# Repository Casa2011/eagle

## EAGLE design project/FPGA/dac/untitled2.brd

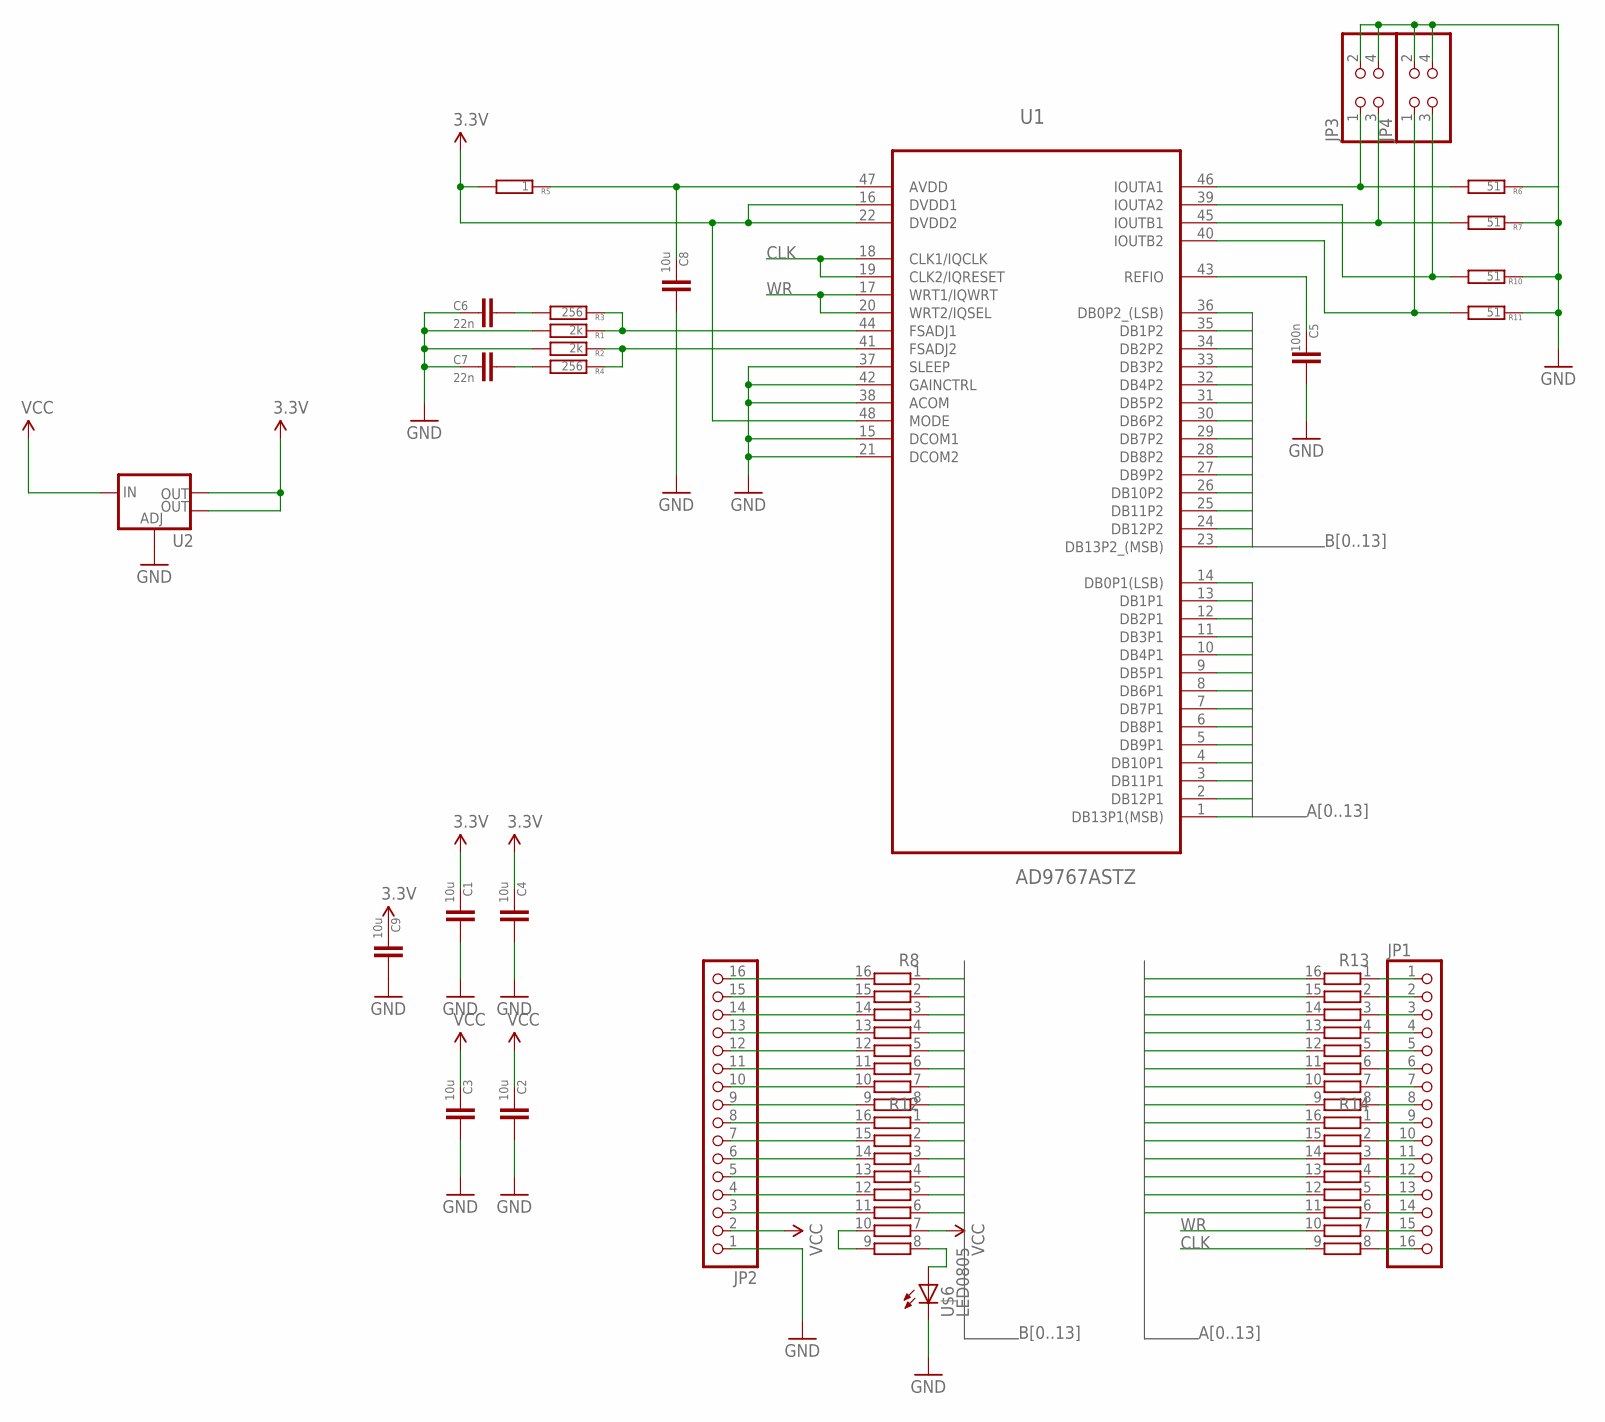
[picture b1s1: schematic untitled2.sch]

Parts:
C1, C2, C3, C4, C8, C9: 10u; C0805
C5: 100n; C0805
C6, C7: 22n; C0805
JP1, JP2: PINHD-1X16_2.54; 1X16
JP3, JP4: PINHD-2X02_2.54-SMD; 2X02SMD
R1, R2: 2k; R0805
R3, R4: 256; R0805
R5: 1; 0603
R6, R7, R10, R11: 51; R0805
R8, R12, R13, R14: 4816P-T01; 4816P
U1: AD9767ASTZ; QFP50P900X900X160-48N
U2: V_REG_LM1117SOT223; SOT223
U$6: LED0805; 0805-LED

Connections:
3.3V: C1.2, C4.2, C9.2, R5.2, U1.16 (DVDD1), U1.22 (DVDD2), U1.48 (MODE), U2.2 (OUT), U2.4 (OUT)
A0: R14.11, U1.14 (DB0P1(LSB))
A1: R14.12, U1.13 (DB1P1)
A2: R14.13, U1.12 (DB2P1)
A3: R14.14, U1.11 (DB3P1)
A4: R14.15, U1.10 (DB4P1)
A5: R14.16, U1.9 (DB5P1)
A6: R13.9, U1.8 (DB6P1)
A7: R13.10, U1.7 (DB7P1)
A8: R13.11, U1.6 (DB8P1)
A9: R13.12, U1.5 (DB9P1)
A10: R13.13, U1.4 (DB10P1)
A11: R13.14, U1.3 (DB11P1)
A12: R13.15, U1.2 (DB12P1)
A13: R13.16, U1.1 (DB13P1(MSB))
B0: R8.1, U1.36 (DB0P2_(LSB))
B1: R8.2, U1.35 (DB1P2)
B2: R8.3, U1.34 (DB2P2)
B3: R8.4, U1.33 (DB3P2)
B4: R8.5, U1.32 (DB4P2)
B5: R8.6, U1.31 (DB5P2)
B6: R8.7, U1.30 (DB6P2)
B7: R8.8, U1.29 (DB7P2)
B8: R12.1, U1.28 (DB8P2)
B9: R12.2, U1.27 (DB9P2)
B10: R12.3, U1.26 (DB10P2)
B11: R12.4, U1.25 (DB11P2)
B12: R12.5, U1.24 (DB12P2)
B13: R12.6, U1.23 (DB13P2_(MSB))
CLK: R14.9, U1.18 (CLK1/IQCLK), U1.19 (CLK2/IQRESET)
GND: C1.1, C2.1, C3.1, C4.1, C5.1, C6.2, C7.2, C8.1, C9.1, JP2.1, JP3.2, JP3.4, JP4.2, JP4.4, R1.2, R2.2, R6.1, R7.1, R10.1, R11.1, U1.15 (DCOM1), U1.21 (DCOM2), U1.37 (SLEEP), U1.38 (ACOM), U1.42 (GAINCTRL), U2.1 (ADJ), U$6.C
unnamed: JP1.1, R13.1
unnamed: JP1.2, R13.2
unnamed: JP1.3, R13.3
unnamed: JP1.4, R13.4
unnamed: JP1.5, R13.5
unnamed: JP1.6, R13.6
unnamed: C8.2, R5.1, U1.47 (AVDD)
unnamed: C6.1, R3.2
unnamed: C7.1, R4.2
unnamed: JP1.7, R13.7
unnamed: JP1.8, R13.8
unnamed: JP1.9, R14.1
unnamed: R1.1, R3.1, U1.44 (FSADJ1)
unnamed: C5.2, U1.43 (REFIO)
unnamed: R2.1, R4.1, U1.41 (FSADJ2)
unnamed: JP1.10, R14.2
unnamed: JP1.11, R14.3
unnamed: JP1.12, R14.4
unnamed: JP1.13, R14.5
unnamed: JP1.14, R14.6
unnamed: JP1.15, R14.7
unnamed: JP1.16, R14.8
unnamed: JP2.16, R8.16
unnamed: JP2.15, R8.15
unnamed: R12.8, U$6.A
unnamed: JP2.14, R8.14
unnamed: JP2.13, R8.13
unnamed: JP2.12, R8.12
unnamed: JP2.11, R8.11
unnamed: JP2.10, R8.10
unnamed: JP2.9, R8.9
unnamed: JP2.8, R12.16
unnamed: JP2.7, R12.15
unnamed: JP2.6, R12.14
unnamed: JP2.5, R12.13
unnamed: JP2.4, R12.12
unnamed: JP2.3, R12.11
unnamed: R12.9, R12.10
O1N: JP3.3, R7.2, U1.45 (IOUTB1)
O1P: JP3.1, R6.2, U1.46 (IOUTA1)
O2N: JP4.1, R11.2, U1.40 (IOUTB2)
O2P: JP4.3, R10.2, U1.39 (IOUTA2)
VCC: C2.2, C3.2, JP2.2, R12.7, U2.3 (IN)
WR: R14.10, U1.17 (WRT1/IQWRT), U1.20 (WRT2/IQSEL)

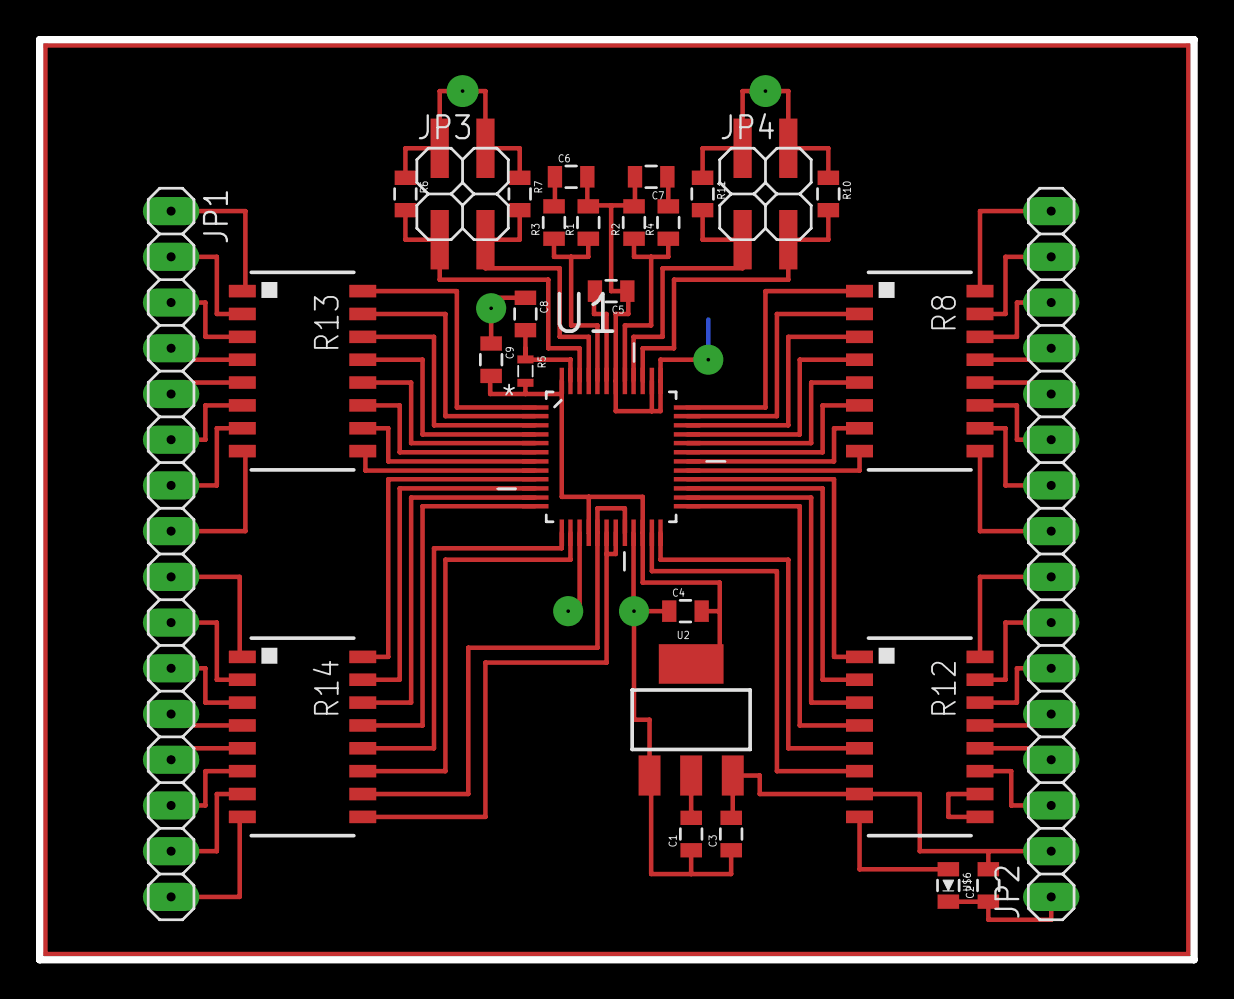
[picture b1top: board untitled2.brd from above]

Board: 2 copper layers, 64.1 x 51.1 mm, 29 parts (0 on the bottom side), 75 nets.

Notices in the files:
parts and their libraries:
SparkFun-PowerIC: Licensing: Creative Commons ShareAlike 4.0 International - https://creativecommons.org/licenses/by-sa/4.0
